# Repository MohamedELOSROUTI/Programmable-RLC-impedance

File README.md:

# Programmable RLC impedance

The main objective of this project is to implement a programmable RLC impedance. This circuit must cover the entire inductive-resistive-capacitive range (voltage/current phase shift between -90° and +90°). The RLC load must be able to dissipate up to 5 W. Two different implementations are suggested: the analog and digital RLC impedance. A programmable RLC impedance with adjustable R, L and C can be useful to simulate the load of a generator like a motor for example. 

## Analog impedance

The first step is to design an analog impedance. A gyrator is used in order to simulate an non ideal inductor with parallel redundant resistor. The main property of the gyrator is to invert the current-voltage characteristic of an electrical component. This way, a capacitor can be used to get a non-ideal variable inductor. The inductance can be adjusted with simple potentiometers. The second step consists in removing the parallel resistors in order to simulate an ideal inductor and reach the 90° phase-shift. This objective can be achieved by connecting the Negative Impedance Converter (N.I.C) in parallel to the gyrator. After that, a more detailed study of the output current and output voltage across the op amps allows to highlight the main limitations of such circuit : see technical report .pdf

The gyrated capacitor and inductor can be connected in parallel with a potentiometer to simulate a programmable RLC impedance as shown here under : 

**<center>Figure 1 : Kicad schematics</center>**

**<center>Figure 2 : Kicad PCB footprint </center>**

As can be seen from Figure 2, three potentiometers are placed at the top of the PCB to adjust the resistive impedance (R_var), and the inductive impedance (R5_indu and R2_indu). On the other hand, R4_capa is a potentiometer used to adjust the capacitive impedance.

The size of the printed circuit track related to the generator and the opamp power supply is chosen larger to decrease as much as possible the voltage drop (and parasitic resistance).

The red track and the green track correspond respectively to the top layer bottom layer of the PCB.

The four power opamps are placed along the same row to make easy the connection of a radiator in case of high power dissipation.

More details about the choice of the components are explained in the following article (or see ): 

https://www.researchgate.net/publication/342452048_Simulation_of_a_programmable_RLC_impedance_Analog_and_digital_implementation

**<center>Figure 3 : 3D Kicad PCB top layer </center>**

**<center>Figure 4 : 3D Kicad PCB bottom layer </center>**

**<center>Figure 5 : 3D Kicad PCB oblique view </center>**

# List of components used

1. Opamps : https://www.mouser.be/ProductDetail/Texas-Instruments/OPA548T?qs=wgAEGBTxy7kyuDG8paPgyg%3D%3D
2. Potentiometers : 
    - Adjustable Gyrated capacitor : https://www.mouser.be/ProductDetail/Bourns/PTV09A-4015U-B503?qs=pxDZlBjcsChjgaXxrSM7Lg==
    - Adjustable Gyrated inductor : https://www.mouser.be/ProductDetail/Bourns/93R1A-R22-A12L?qs=%2Fha2pyFadujN8NjAXMmLjGFZb2gaUmOwtYIhbzFhkfaZK5uBbZHutQ%3D%3D
    - Adjustable Resistor : https://www.mouser.be/ProductDetail/Bourns/96R1A-R16-A15L?qs=iuQ%252BhjgTeig0Okk2%252Boma3A==
3. Switches : https://www.mouser.be/ProductDetail/CK/FP12SPC1B1TP00?qs=%2Fha2pyFadujdL%2FKUzrOTABrsLBJn1GvGCS2%252BuxUnWEOCBKVtXu80Ug%3D%3D
## Digital impedance

The second step consists in designing a digital RLC impedance. By contrast to the analog impedance, the filtering process is done digitally using a microcontroller. A software feedback control approach is employed to adjust the current amplitude and the power factor regarding the input voltage.

The objective is to maintain the impedance value constant regardless of the variation of the source voltage amplitude. Many paramaters such as the sampling frequency and the resolution of the ADC/DAC may affect the quality of the output current. The voltage can be converted to current using the Howland current source. Several simulations have been performed to visualise the performance of the digital RLC filter. See technical report .pdf.

However, another circuit made of only one opamp with negative feedback called transconductance amplifier can be used to convert the input voltage into current and inject it in the generator. It acts like a current source. The transconductance ratio is fixed by the value of the resistor R1. The Current I = Vin/R. The transconductance amplifier will be used here thanks to its simplicity (only makes use of one resistor to fix the output current). For more details, get a look at : 
 https://www.allaboutcircuits.com/textbook/semiconductors/chpt-8/voltage-to-current-signal-conversion/

**<center>Figure 1 : Transconductance amplifier simplified</center>**

Choosing R = 1 Ohm insures that Vin is a "perfect" image of the output current delivered by the generator. Let's assume that we want to simulate a 1 mF capacitor (C = 1 mF). The amplitude of the output current I should be equal to : I = Vgenerator.w.C (w=2*pi*f). Thus, the microcontroller should be able to measure at each time step the sample Vgenerator (through a ADC) and cpmpute Vin = I to simulate a constant 1 mF capacitor. A digital RLC filter must be implemented in the microcontroller. Thus a DAC is necessary to convert the digital voltage to analog voltage through the positive input of the transconductance unity gain amplifier.

More details about the implementation of the digital RLC filter can be found in technical report.pdf. The choice of the sampling frequency is crucial if one desires to maintain a phase-shift of +/- 90 degrees between input voltage and output current for ideal components (inductor/capacitor). The Z-transform allows to highlight the behaviour of the phase and magnitude depending on the sampling frequency.

Warning : One of the pins of the generator mustn't be connected to GND. Otherwise, the output if the transconductance opamp can be shorted. However, the howland current source allows to deal with grounded generators.

A special care has to be taken regarding the input voltage. A unity gain instrumentation amplifier with its high input impedance is used in order to "capture" Vgenerator at the output. The INA103 is used for this purpose. Before, connecting the output of the INA103 (Vgenerator) to input pin of the 12 bits ADC, we have to make sure that it is between 0 and 5 V. To reach the objective, a voltage divider made up with 2 equal resistors are used (5,11k Ohms). It is supplied between Vgenerator and V++ (positive supply voltage of the opamp). This will add (Vgenerator + V++)/2 to Vgenerator and make sure that the input is positive. Another voltage divider (1/4) allows to rescale Vgenerator between 0 and 5 V and feed it into the ADC. 

**<center>Figure 2 : Digital RLC impedance global overview</center>**

Important note regarding the 1 Ohm resistor that fixes the transconductance ratio : since the OPA548 output is internally buffered (can reach 5A peak), the resistor shall be able to dissipate up to 25 W. Thus the choice of the resistor is important here. Furthermore, the tolerance value shall also be low in order to keep the ratio as close as possible to 1. 

The LTO100 (F1R000FTE3) thick film power resistor can be a good candidate with its 1% tolerance.

**<center>Figure 3 : Kicad Schematics </center>**
Here's the Kicad schematics with the components used for building the digital programmable RLC impedance:

**<center>Figure 4 : Kicad PCB footprint</center>**

Here is the PCB footprint of the digital RLC impedance. The red/green circuit track corresponds respectively to the top/bottom side of the PCB. A special care has been taken to deal with high current (5 A). Thicker circuit tracks have been chosen to supply the op amps. Since the 1 Ohm resistor can afford 5 Amps, it's also important to make sure that the copper circuit track doesn't add parasitic resistance (and thus dissipation of power).

2x4 pins headers have been added to connect both the ADC and the DAC to the microcontroller. The serial communication protocole used is the I2C using SDA/SCL signals. 

**<center>Figure 5 : 3D Kicad PCB top layer </center>**
Only footprints            |  With components
:-------------------------:|:-------------------------:
|

**<center>Figure 6 : 3D Kicad PCB bottom layer </center>**
Only footprints             |  With components
:-------------------------:|:-------------------------:
 |

**<center>Figure 7 : 3D Kicad PCB oblique view </center>**

# List of components used

1. Opamp OPA 548: https://www.mouser.be/ProductDetail/Texas-Instruments/OPA548T?qs=wgAEGBTxy7kyuDG8paPgyg%3D%3D
3. Data converters : 
    - DAC : https://www.ti.com/product/DAC60502#design-development##cad-cae-symbols
    - ADC : https://www.ti.com/lit/ds/symlink/adc121c021.pdf?ts=1626049868732
3. Power resistoir : https://www.mouser.be/ProductDetail/Vishay-Sfernice/LTO100F1R000FTE3?qs=%2Fha2pyFadugIVD2ktmO4cgaopqaUXUdcjnQSGuVaM89tHJq5NFeucw%3D%3D
4. Voltage regulator : https://www.mouser.be/ProductDetail/Texas-Instruments/TPS7B8450QDCYRQ1?qs=%2Fha2pyFaduj2%252B%252BpD6KOjDCj45zFJpH97QDune9sg%2F3aik8Y5MlUrEg%3D%3D
5. Instrumentation op amp INA103 : https://www.ti.com/product/INA103#design-development

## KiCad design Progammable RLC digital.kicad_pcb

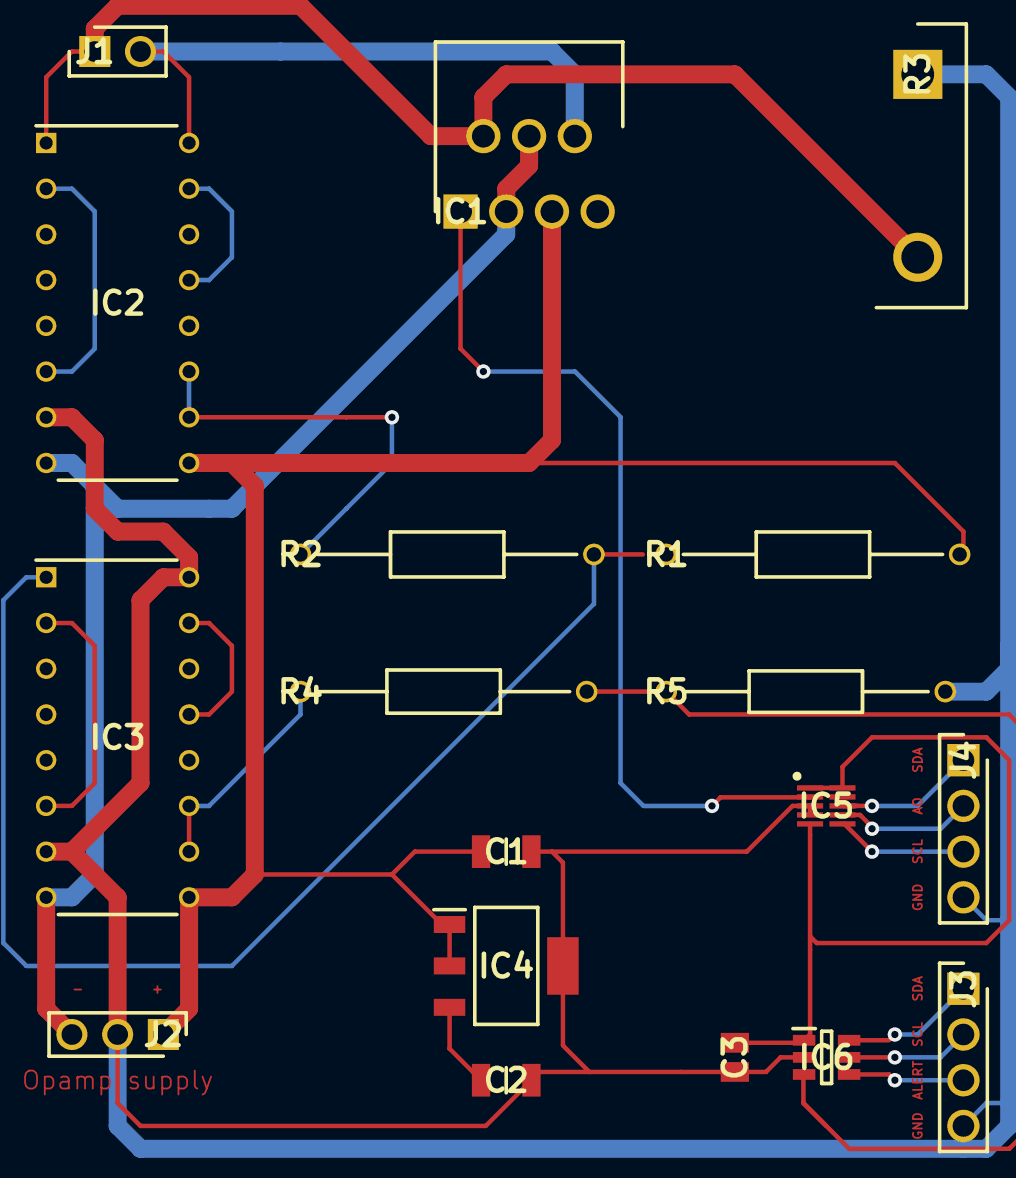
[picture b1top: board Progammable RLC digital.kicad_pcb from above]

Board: 2 copper layers, 18 parts (0 on the bottom side), 22 nets.

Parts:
C1, C2: 12061C225KAT4A; CAPC3216X178N
C3: C0805X154K5RAC7800; CAPC2012X100N
IC1: OPA548TG3; TO127P470X1016X2195-7P
IC2, IC3: INA103KP; DIP794W53P254L1930H508Q16N
IC4: TPS7B8450QDCYRQ1; SOT230P700X180-4N
IC5: DAC60502DRXR; SON50P250X250X80-10N
IC6: ADC121C021CIMK_NOPB; SOT95P280X110-6N
J1: 10129378-902001BLF; HDRV2W67P0X254_1X2_508X241X843P
J2: 10129378-903001BLF; HDRV3W67P0X254_1X3_762X241X858P
J3, J4: G800W304018EU; HDRV4W69P0X254_1X4_1016X250X895P
R1, R2: MBB02070E5111BC100; RESAD1630W60L630D250
R3: LTO100F1R000FTE3; TO1016P500X1576X2420-2P
R4: MFR-25FTE52-30K; RESAD1590W60L630D240
R5: YR1B10KCC; RESAD1550W60L630D230

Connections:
ADC_ALERT: IC6.4, J3.3
ADC_SCL: IC6.5, J3.2
ADC_SDA: IC6.6, J3.1
DAC_A0: IC5.7, J4.2
DAC_SCL: IC5.6, J4.3
DAC_SDA: IC5.8, J4.1
GND: C1.2, C2.2, C3.1, IC2.7, IC3.7, IC3.16, IC4.4, IC5.3, IC5.4, IC6.2, J2.2, J3.4, J4.4, R3.1, R5.2
unnamed: IC2.2, IC2.6
unnamed: IC2.13, IC2.15
unnamed: IC3.1, R1.1, R2.2
unnamed: IC3.2, IC3.6
unnamed: IC3.10, IC3.11, R4.1
unnamed: IC3.13, IC3.15
V_adc_dac: C3.2, IC5.1, IC5.5, IC5.10, IC6.1
Vadc_dac: C2.1, IC4.3
Vdiff: IC2.10, IC2.11, R2.1
Vfilter: IC1.1, IC5.2
Vgenerator+: IC1.2, IC2.1, J1.1, R3.2
Vgenerator-: IC1.6, IC2.16, J1.2
Vin_ADC: IC6.3, R4.2, R5.1
Vsupply+: C1.1, IC1.5, IC2.9, IC3.9, IC4.1, IC4.2, J2.1, R1.2
Vsupply-: IC1.3, IC1.4, IC2.8, IC3.8, J2.3

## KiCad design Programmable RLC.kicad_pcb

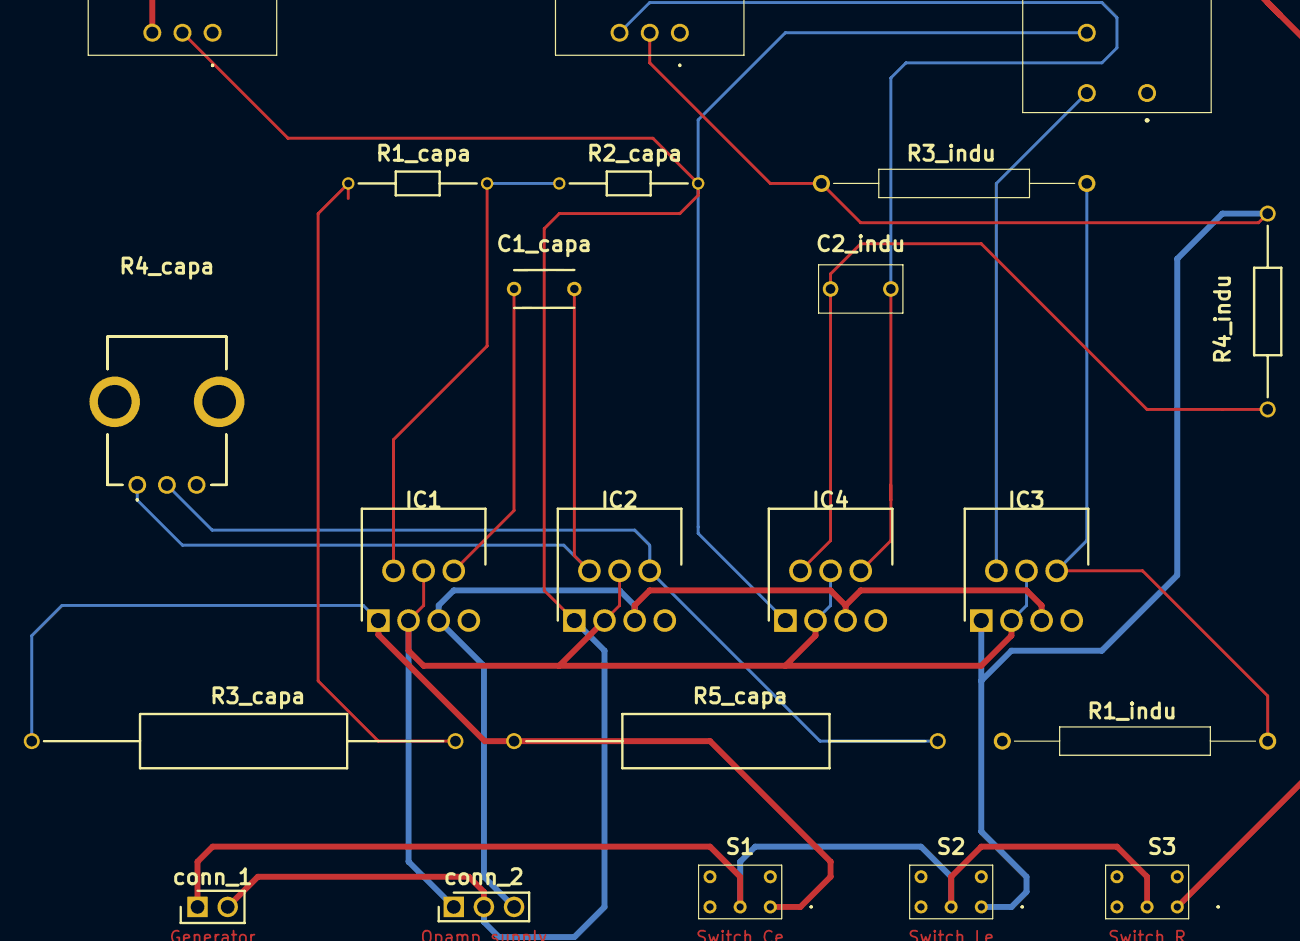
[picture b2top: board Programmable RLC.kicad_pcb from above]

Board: 2 copper layers, 22 parts (0 on the bottom side), 16 nets.

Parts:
C1_capa: SR215A 1nF; SR215A102FARTR1
C2_indu: C330C105J5R5TA
IC1, IC2, IC3, IC4: OPA548TG3; TO127P470X1016X2195-7P
R1_capa, R2_capa: MFR3-10KFC; RESAD1170W45L370D200
R1_indu, R3_indu: MG660-500-1%; MG6605001
R2_indu: 93R1A-R22-A12L; 93R1AR22A12L
R3_capa, R5_capa: CMF655K0000FKEB; RESAD3573W69L1745D457
R4_capa: PTV09A-4015U-B503; PTV09A4015UB503
R4_indu: CMF551K0000BHEB; RESAD1653W69L737D229
R5_indu: 96R1A-R16-A15L; 96R1AR16A15L
R_var: 96R1A-R16-A15L; 96R1AR16A15L
S1, S2, S3: FP12SPC1B1TP00
conn_1: 10129378-902001BLF; HDRV2W67P0X254_1X2_508X241X843P
conn_2: 10129378-903001BLF; HDRV3W67P0X254_1X3_762X241X858P

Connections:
GND: IC2.1, IC4.1, R2_capa.2, R2_indu.2, R_var.R2, conn_1.2, conn_2.2
unnamed: C1_capa.1, IC1.6
unnamed: C1_capa.2, IC2.2, R4_capa.1
unnamed: C2_indu.1, IC4.2, R4_indu.2
unnamed: C2_indu.2, IC4.6, R5_indu.R3
unnamed: IC1.2, R1_capa.2, R2_capa.1
unnamed: IC2.6, R4_capa.2, R5_capa.2
unnamed: IC3.2, R1_indu.2, R2_indu.3
unnamed: IC3.6, R1_indu.1, R3_indu.1
unnamed: R1_capa.1, R3_capa.2
Vgenerator: S1.2, S2.2, S3.2, conn_1.1
VgyratedCapa: IC1.1, R3_capa.1, R5_capa.1, S1.1
VgyratedIndu: IC3.1, R3_indu.2, R4_indu.1, R5_indu.R2, S2.1
Vresistor: R_var.R3, S3.1
Vs++: IC1.5, IC2.5, IC3.5, IC4.5, conn_2.3
Vs--: IC1.3, IC1.4, IC2.3, IC2.4, IC3.3, IC3.4, IC4.3, IC4.4, conn_2.1
